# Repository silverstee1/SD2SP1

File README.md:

# SD2SP1
MicroSD adapter PCB for SP1 on Nintendo GameCube

Due to the way the SP1 port is handled on the gamecube the speeds of the adapter are limited to v1.0 speeds like the original adapters for other ports, ex. WiiSD, GC2SD, SD2SP2 which didn't have added OR gate component to achieve the higher v2.0 speeds.

Make sure to use the latest version of Swiss in order to use this adapter in SP1 Slot on the bottom of the gamecube, the pcb is marked which orientation it is to be inserted and can be covered with SP1 Port cover once installed.

https://github.com/emukidid/swiss-gc

# PCB Order

Make sure to order the PCB from a fab such as JLCPCB with a 1.2mm thickness and a ENIG surface finish for longevity, HASL will work too but won't be as durable on the edge connector in the long run.

# BOM

| Designator | Description | DigiKey Part # | LCSC Part # |
| --- | --- | --- | --- |
| C1 | 0402 22u Capactior (10V Min) | 490-GRM158R61A226ME15DCT-ND | C3845593 |
| J1 | MicroSD Slot | 2223-MSD-4-ACT-ND | C113206 |
| PCB | Order From Fab ex. JLCPCB 1.2mm thickness ENIG |||

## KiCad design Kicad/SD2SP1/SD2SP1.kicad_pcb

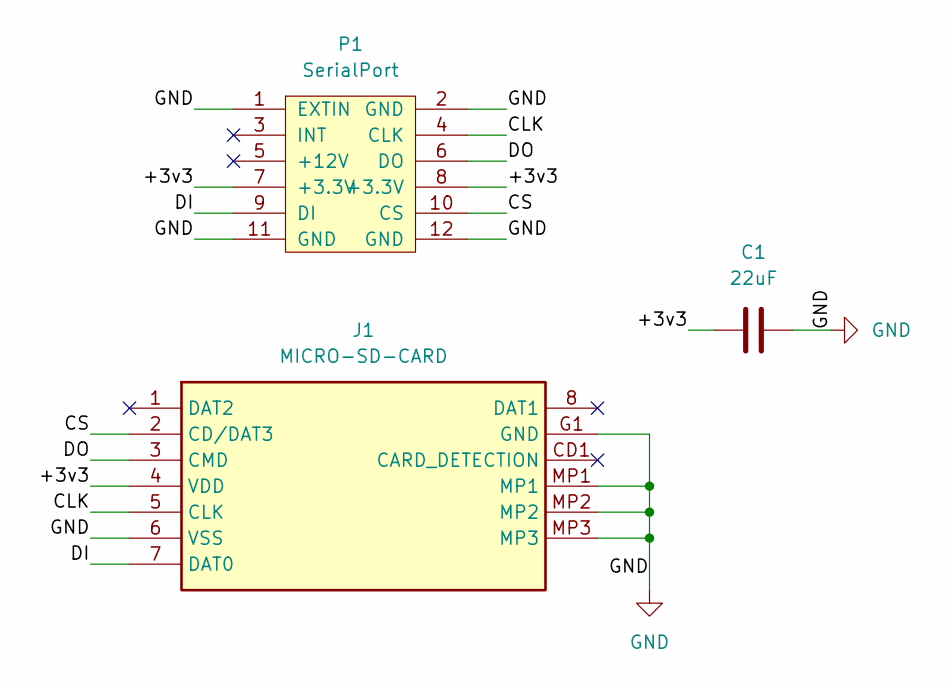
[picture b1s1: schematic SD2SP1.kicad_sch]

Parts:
C1: 22uF; C_0402_1005Metric_Pad0.74x0.62mm_HandSolder
J1: MICRO-SD-CARD; MICROSDCARD; Mouser Part Number 909-MICRO-SD-CARD
P1: SerialPort; SP1_FootPrint

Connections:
/+3v3: C1.1, J1.4 (VDD), P1.7 (+3.3V), P1.8 (+3.3V)
/CLK: J1.5 (CLK), P1.4 (CLK)
/CS: J1.2 (CD/DAT3), P1.10 (CS)
/DI: J1.7 (DAT0), P1.9 (DI)
/DO: J1.3 (CMD), P1.6 (DO)
GND: C1.2, J1.6 (VSS), J1.G1 (GND), J1.MP1, J1.MP2, J1.MP3, P1.1 (EXTIN), P1.2 (GND), P1.11 (GND), P1.12 (GND)

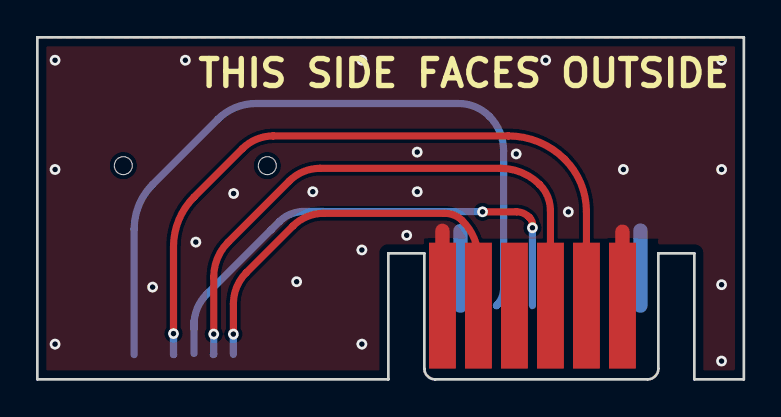
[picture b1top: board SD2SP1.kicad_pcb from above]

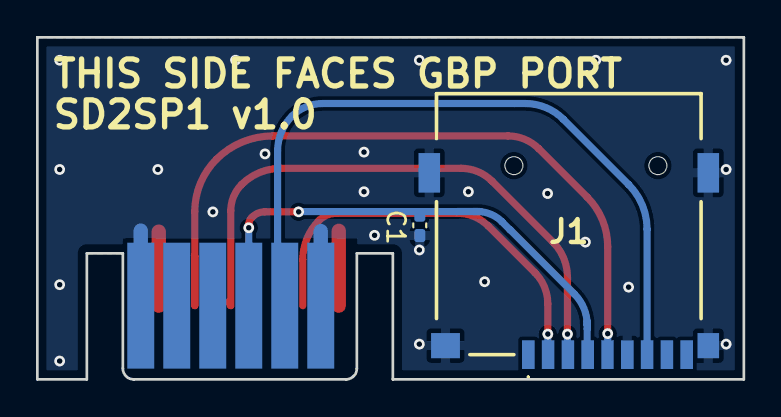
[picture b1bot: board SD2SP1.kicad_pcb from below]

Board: 2 copper layers, 39.2 x 19.0 mm, 3 parts (3 on the bottom side), 6 nets.

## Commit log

2025-03-29 added project and pcb files
